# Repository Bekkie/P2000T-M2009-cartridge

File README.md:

# P2000T M2009-WiFi Cartridge

Use the old M2009 Auto dial/asnwer-modem over WiFi

Wi-Fi modem hardware and firmware for the Philips P2000T home computer. This repository contains an M2009 modem cartridge emulator, a serial Viditel modem emulator, and software for connecting the P2000T to network services.

| M2009 Wi-Fi modem cartridge | Viditel modem emulator |
| --- | --- |
|  |  |
| RP2040/Pico W replacement for the Miniware M2009. | ESP32-based V.24 modem replacement. |

## Start here

- [Hardware designs](docs/hardware.md) - case files, schematic previews and sources, PCB files, and fabrication PDFs.
- [M2009 modem emulator](docs/m2009-modem-emulator.md) - setup, dialing, network services, and P2000T I/O behavior.
- [Viditel modem emulator](docs/viditel-modem-emulator.md) - serial settings, configuration, and supported services.
- [FTP client and server](docs/ftp-client-and-server.md) - using the P2000T FTP client and its server. (works only with M2009-WiFi)
- [Viewdata server](docs/viewdata-server.md) - running and connecting to a local Viewdata host.
- [Firmware build notes](src/README.md) - PlatformIO environments, build commands, and repository layout.

## Build firmware

Install PlatformIO Core, then run these commands from the repository root:

```powershell
pio run -e m2009-emulator
pio run -e viditel-modem-emulator
```

See the [firmware build notes](src/README.md) for upload instructions and details about the FTP client build.

## What does it bring you?

### Take a trip down memory lane

Open your M2009 Terminal program, dial a number, listen to the modem sounds of the 1980s, and watch your P2000T screen slowly fill with old-school graphics.

## Access the P2000T Software Preservation collection

Clone https://github.com/p2000t/software next to this repository on your PC. From the parent directory, start the [FTP server](docs/ftp-client-and-server.md), then run the FTP client on your P2000T to browse and load the preserved software as if there are on JWS-disks.

- Server command: (Winsows examample should olso work on Linux)
```console
C:\Users\<user>\Documents\GitHub>python p2000t-m2009-cartridge\src\test-server\myftpserver.py --port 8082 --file software\disks\*.dsk --file software\cassettes\

*** P2000T FTP Server ****
[START] Searching for media images in: software\disks\*.dsk
[START] Searching for media images in: software\cassettes\
Starting server with 15 'disks'
mDNS-service registreren...
[SERVER] Server running. Listening on port 8082...
```

- P2000T commands (you can download the FPT-client from the internal modem menu, option 5)

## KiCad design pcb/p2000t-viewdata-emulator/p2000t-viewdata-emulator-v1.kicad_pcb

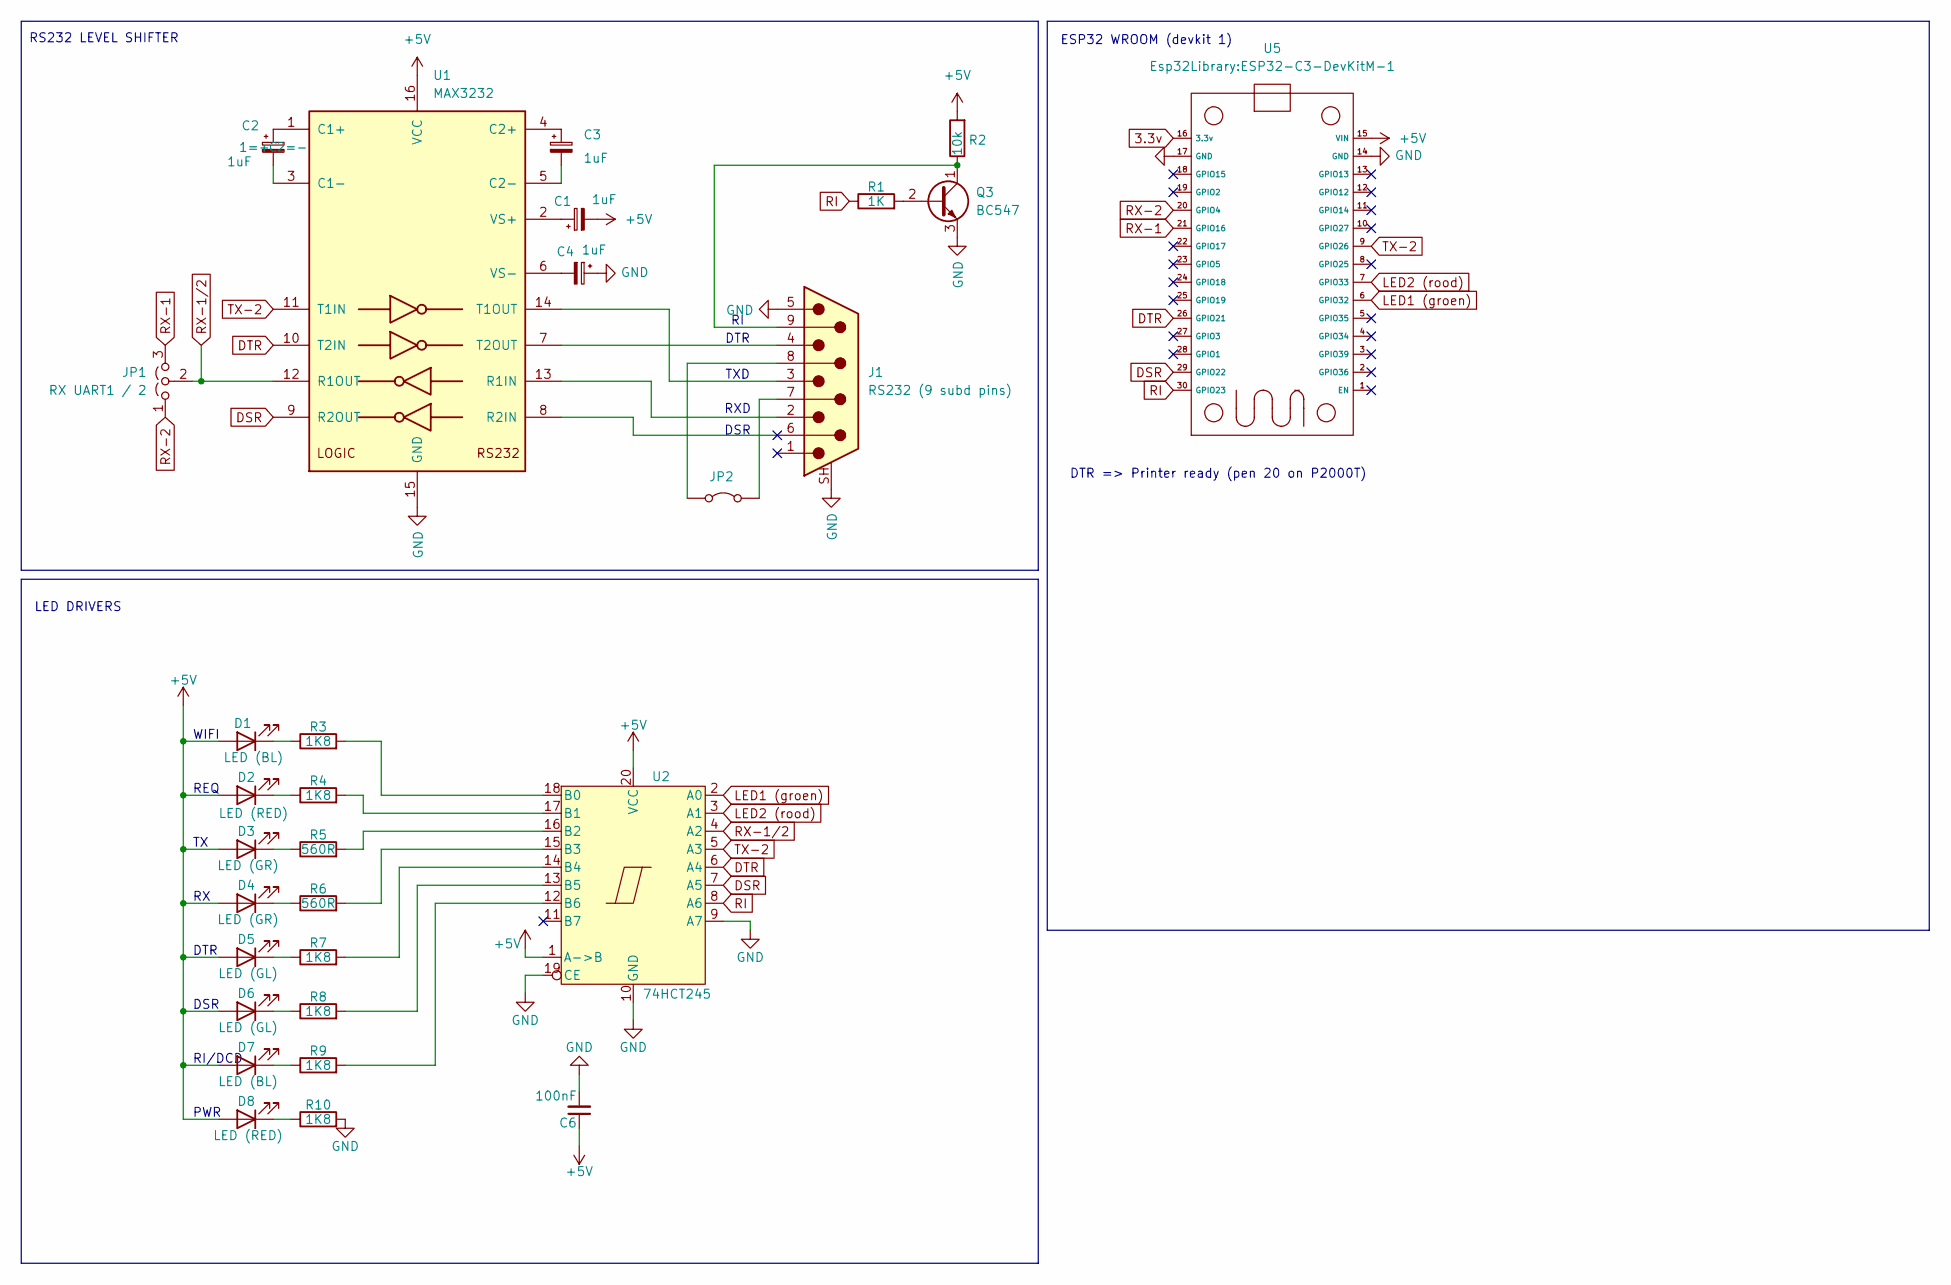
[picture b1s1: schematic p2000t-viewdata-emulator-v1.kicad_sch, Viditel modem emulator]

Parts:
C1, C2, C3, C4: 1uF; C_Disc_D7.5mm_W4.4mm_P5.00mm
C6: 100nF; C_Disc_D5.0mm_W2.5mm_P5.00mm; DigiKey PN 399-9859-1-ND
D1, D7: LED (BL); LED_D3.0mm
D2, D8: LED (RED); LED_D3.0mm
D3, D4: LED (GR); LED_D3.0mm
D5, D6: LED (GL); LED_D3.0mm
J1: RS232 (9 subd pins); DSUB-9_Pins_Horizontal_P2.77x2.84mm_EdgePinOffset4.94mm_Hou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
JP1: RX UART1 / 2; PinHeader_1x03_P2.54mm_Vertical
JP2: Jumper_2_Bridged; PinHeader_1x02_P2.54mm_Vertical
Q3: BC547; TO-92_Inline
R1: 1K; R_Axial_DIN0309_L9.0mm_D3.2mm_P12.70mm_Horizontal
R2: 10k; R_Axial_DIN0309_L9.0mm_D3.2mm_P12.70mm_Horizontal
R3, R4, R7, R8, R9, R10: 1K8; R_Axial_DIN0309_L9.0mm_D3.2mm_P12.70mm_Horizontal
R5, R6: 560R; R_Axial_DIN0309_L9.0mm_D3.2mm_P12.70mm_Horizontal
U1: MAX3232; DIP-16_W7.62mm_Socket_LongPads
U2: 74HCT245; DIP-20_W7.62mm_Socket
U5: ESP32-C3-DevKitM-1

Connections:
3.3v: U5.16 (3.3v)
+5V: C1.2, C6.1, D1.2 (A), D2.2 (A), D3.2 (A), D4.2 (A), D5.2 (A), D6.2 (A), D7.2 (A), D8.2 (A), R2.2, U1.16 (VCC), U2.1 (A->B), U2.20 (VCC), U5.15 (VIN)
DSR: U1.9 (R2OUT), U2.7 (A5), U5.29 (GPIO22)
DTR: U1.10 (T2IN), U2.6 (A4), U5.26 (GPIO21)
GND: C4.1, C6.2, J1.5, J1.SH (PAD), Q3.3 (E), R10.2, U1.15 (GND), U2.9 (A7), U2.10 (GND), U2.19 (CE), U5.14 (GND), U5.17 (GND)
LED1 (groen): U2.2 (A0), U5.6 (GPIO32)
LED2 (rood): U2.3 (A1), U5.7 (GPIO33)
unnamed: D1.1 (K), R3.1
unnamed: D2.1 (K), R4.1
unnamed: D3.1 (K), R5.1
unnamed: D4.1 (K), R6.1
unnamed: D5.1 (K), R7.1
unnamed: D6.1 (K), R8.1
unnamed: D7.1 (K), R9.1
unnamed: D8.1 (K), R10.1
unnamed: J1.8, JP2.1 (A)
unnamed: J1.7, JP2.2 (B)
unnamed: Q3.2 (B), R1.2
unnamed: J1.9, Q3.1 (C), R2.1
unnamed: C2.1, U1.1 (C1+)
unnamed: C2.2, U1.3 (C1-)
unnamed: C3.1, U1.4 (C2+)
unnamed: C3.2, U1.5 (C2-)
unnamed: J1.2, U1.13 (R1IN)
unnamed: J1.3, U1.14 (T1OUT)
unnamed: J1.4, U1.7 (T2OUT)
unnamed: C1.1, U1.2 (VS+)
unnamed: C4.2, U1.6 (VS-)
unnamed: R3.2, U2.18 (B0)
unnamed: R4.2, U2.17 (B1)
unnamed: R5.2, U2.16 (B2)
unnamed: R6.2, U2.15 (B3)
unnamed: R7.2, U2.14 (B4)
unnamed: R8.2, U2.13 (B5)
unnamed: R9.2, U2.12 (B6)
RI: R1.1, U2.8 (A6), U5.30 (GPIO23)
RX-1: JP1.3 (B), U5.21 (GPIO16)
RX-1/2: JP1.2 (C), U1.12 (R1OUT), U2.4 (A2)
RX-2: JP1.1 (A), U5.20 (GPIO4)
TX-2: U1.11 (T1IN), U2.5 (A3), U5.9 (GPIO26)

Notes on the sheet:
DTR
RXD
ESP32 WROOM (devkit 1)
DTR => Printer ready (pen 20 on P2000T)
RI/DCD
TXD
PWR
RS232 LEVEL SHIFTER
WIFI
LED DRIVERS
DSR
REQ

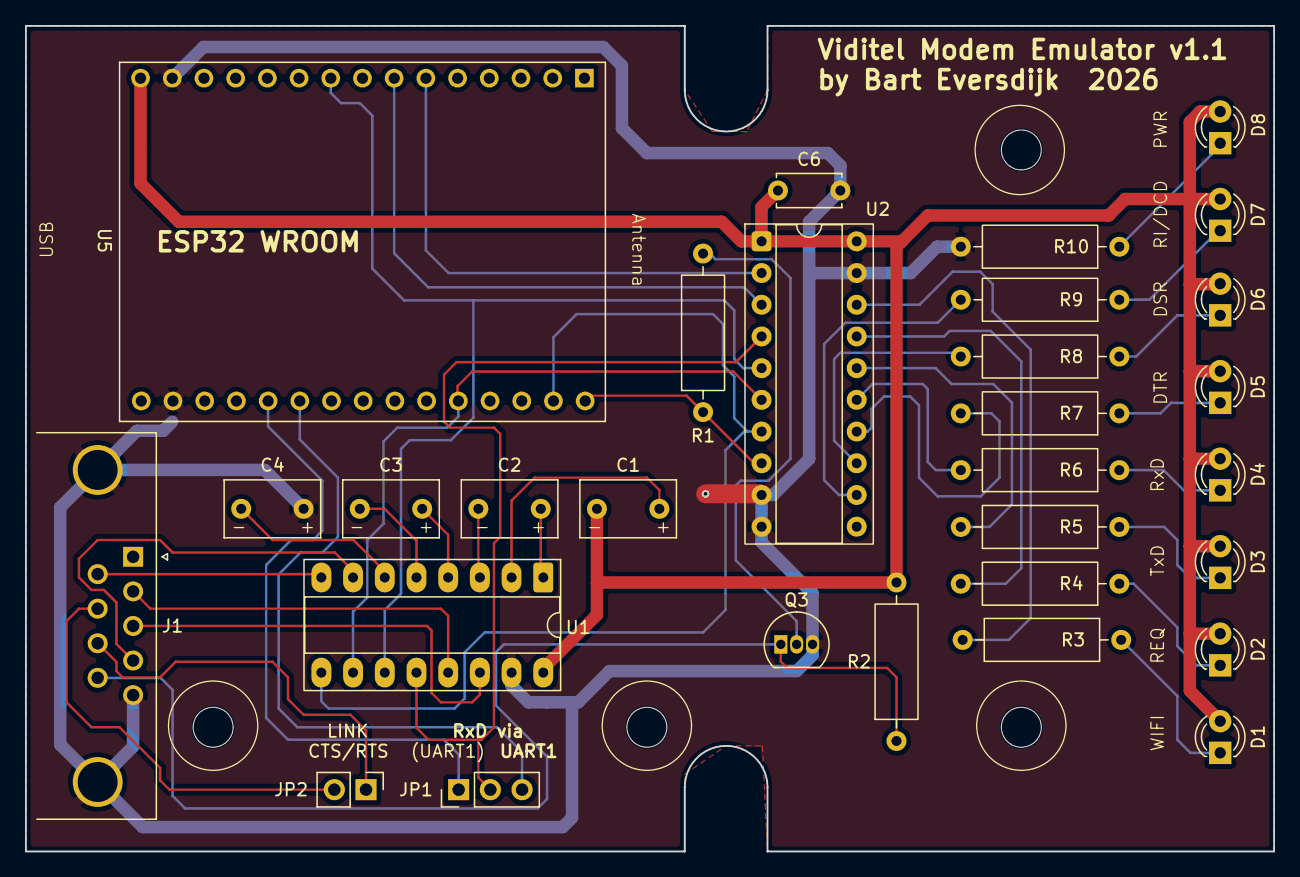
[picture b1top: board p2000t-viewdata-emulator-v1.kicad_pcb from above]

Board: 2 copper layers, 100.0 x 66.1 mm, 30 parts (0 on the bottom side), 39 nets.
